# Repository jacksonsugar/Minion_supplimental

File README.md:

# Minion_supplimental
Additional docs for the Minion.

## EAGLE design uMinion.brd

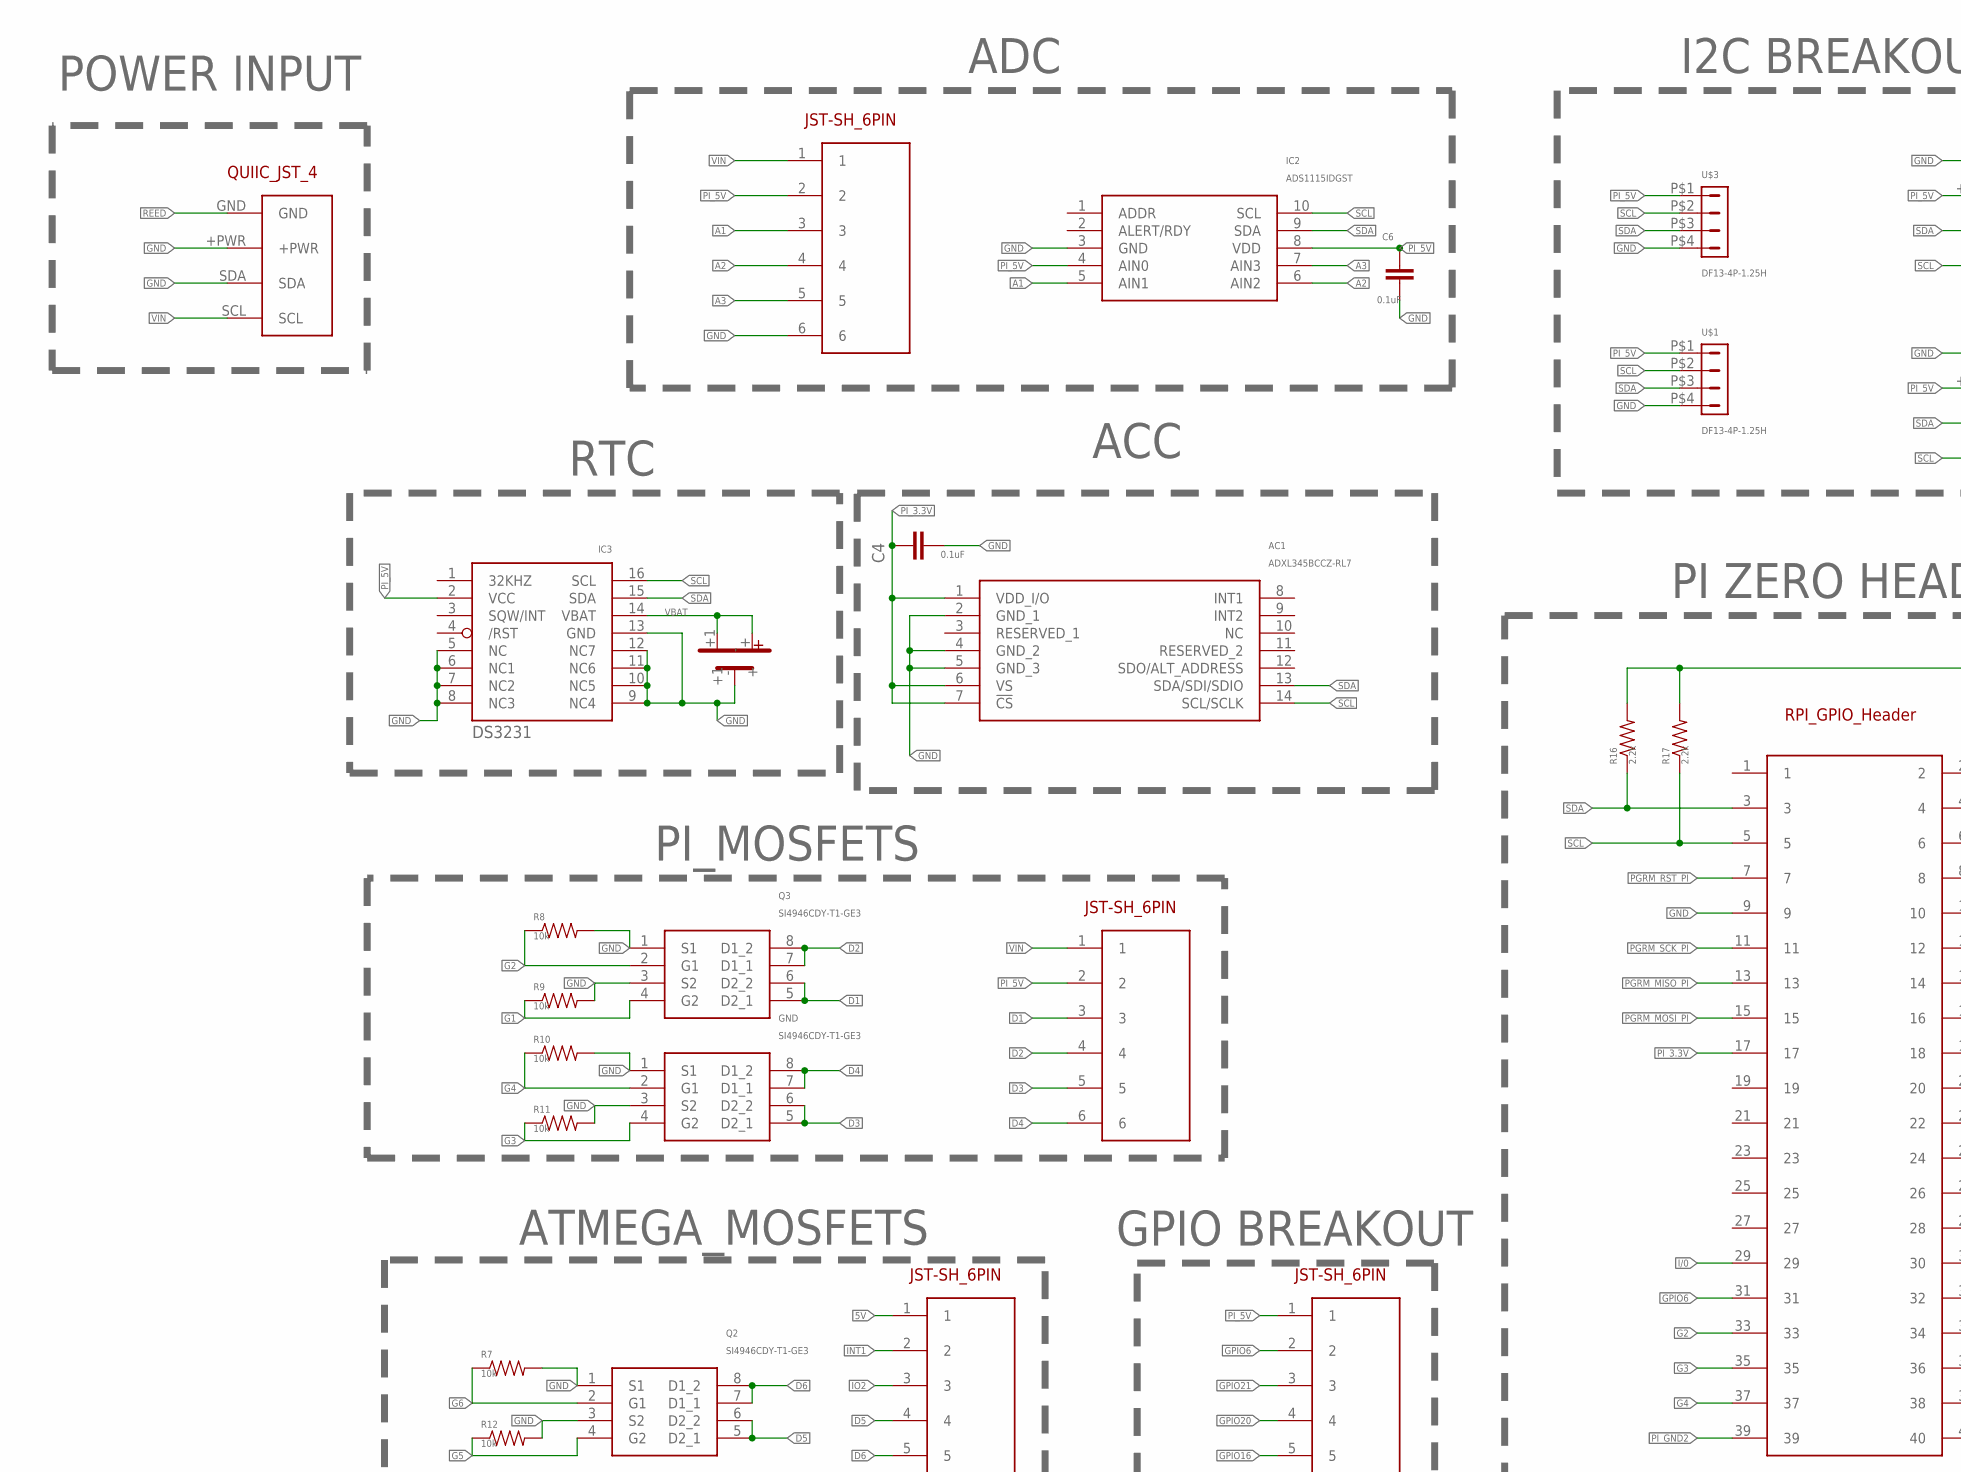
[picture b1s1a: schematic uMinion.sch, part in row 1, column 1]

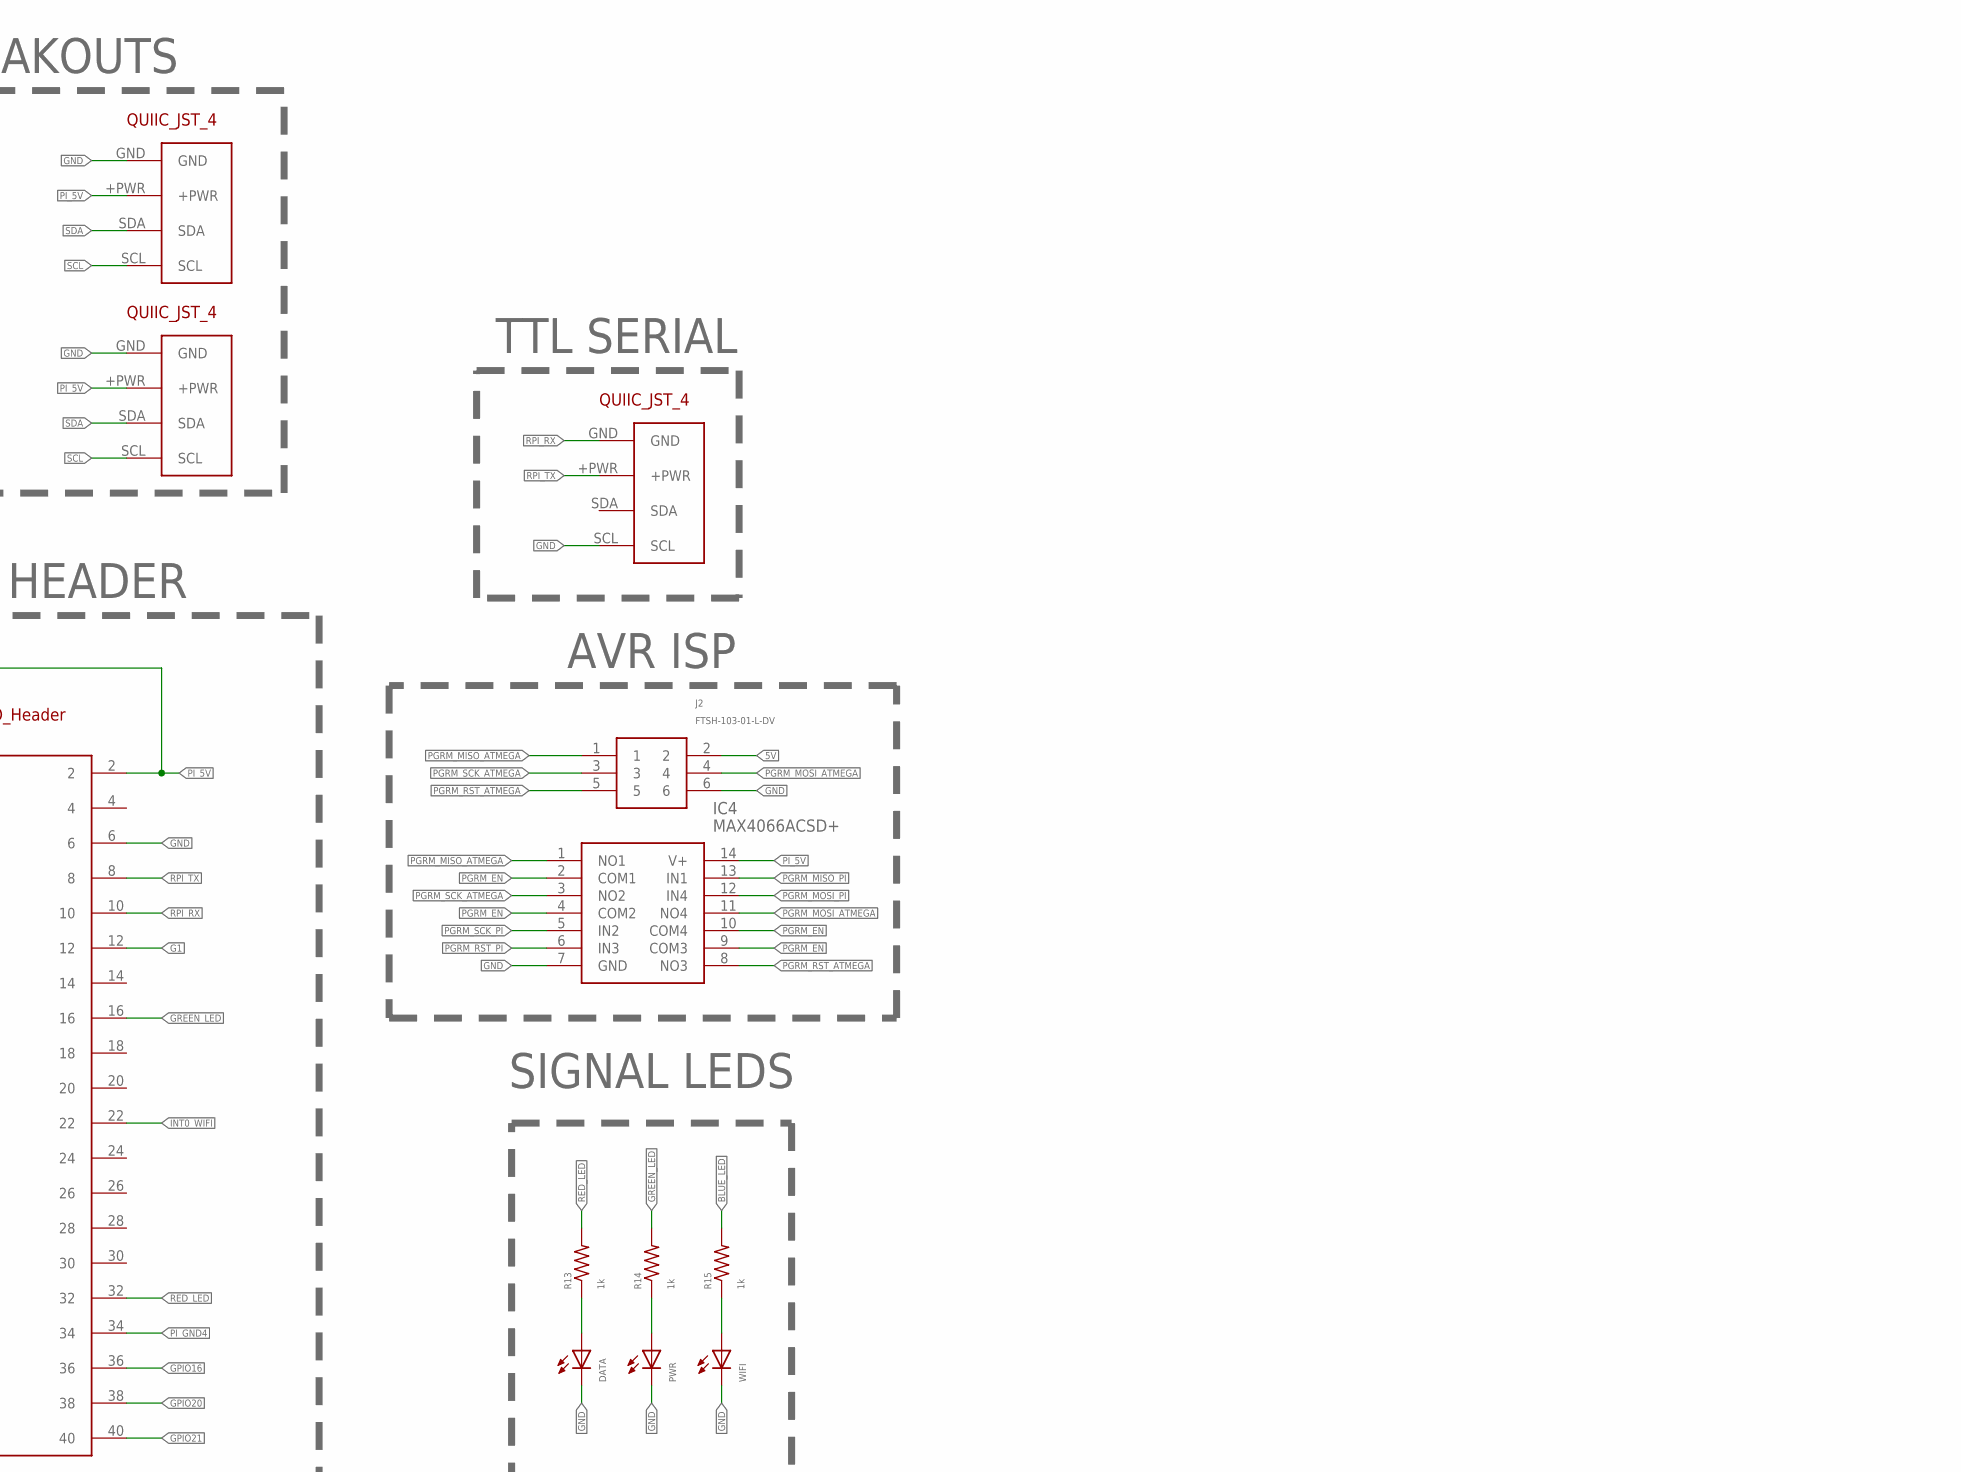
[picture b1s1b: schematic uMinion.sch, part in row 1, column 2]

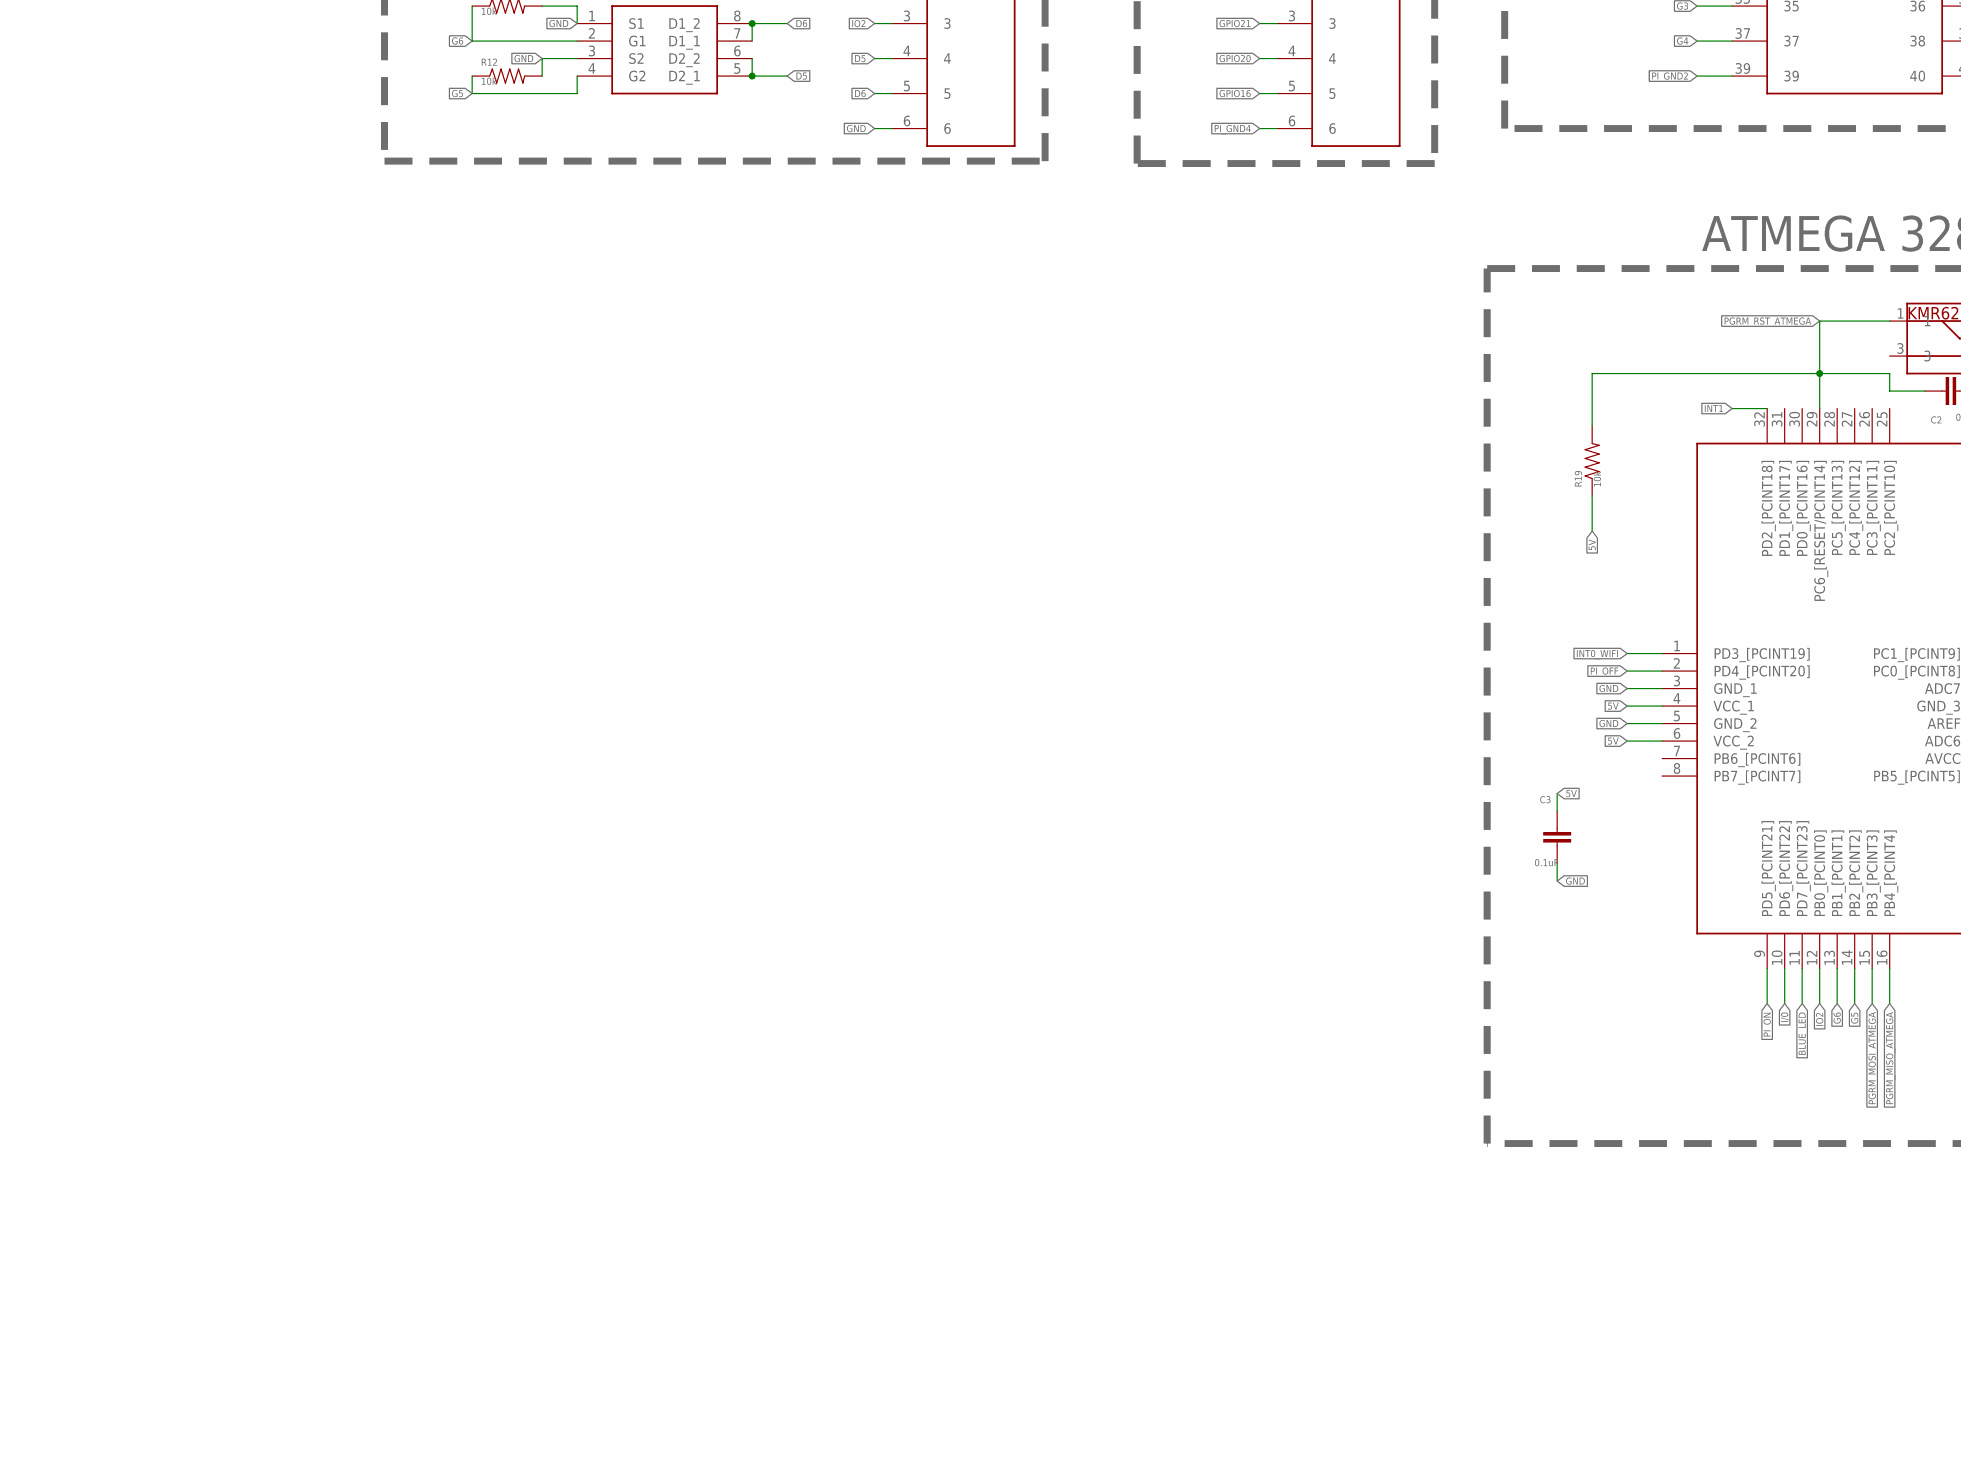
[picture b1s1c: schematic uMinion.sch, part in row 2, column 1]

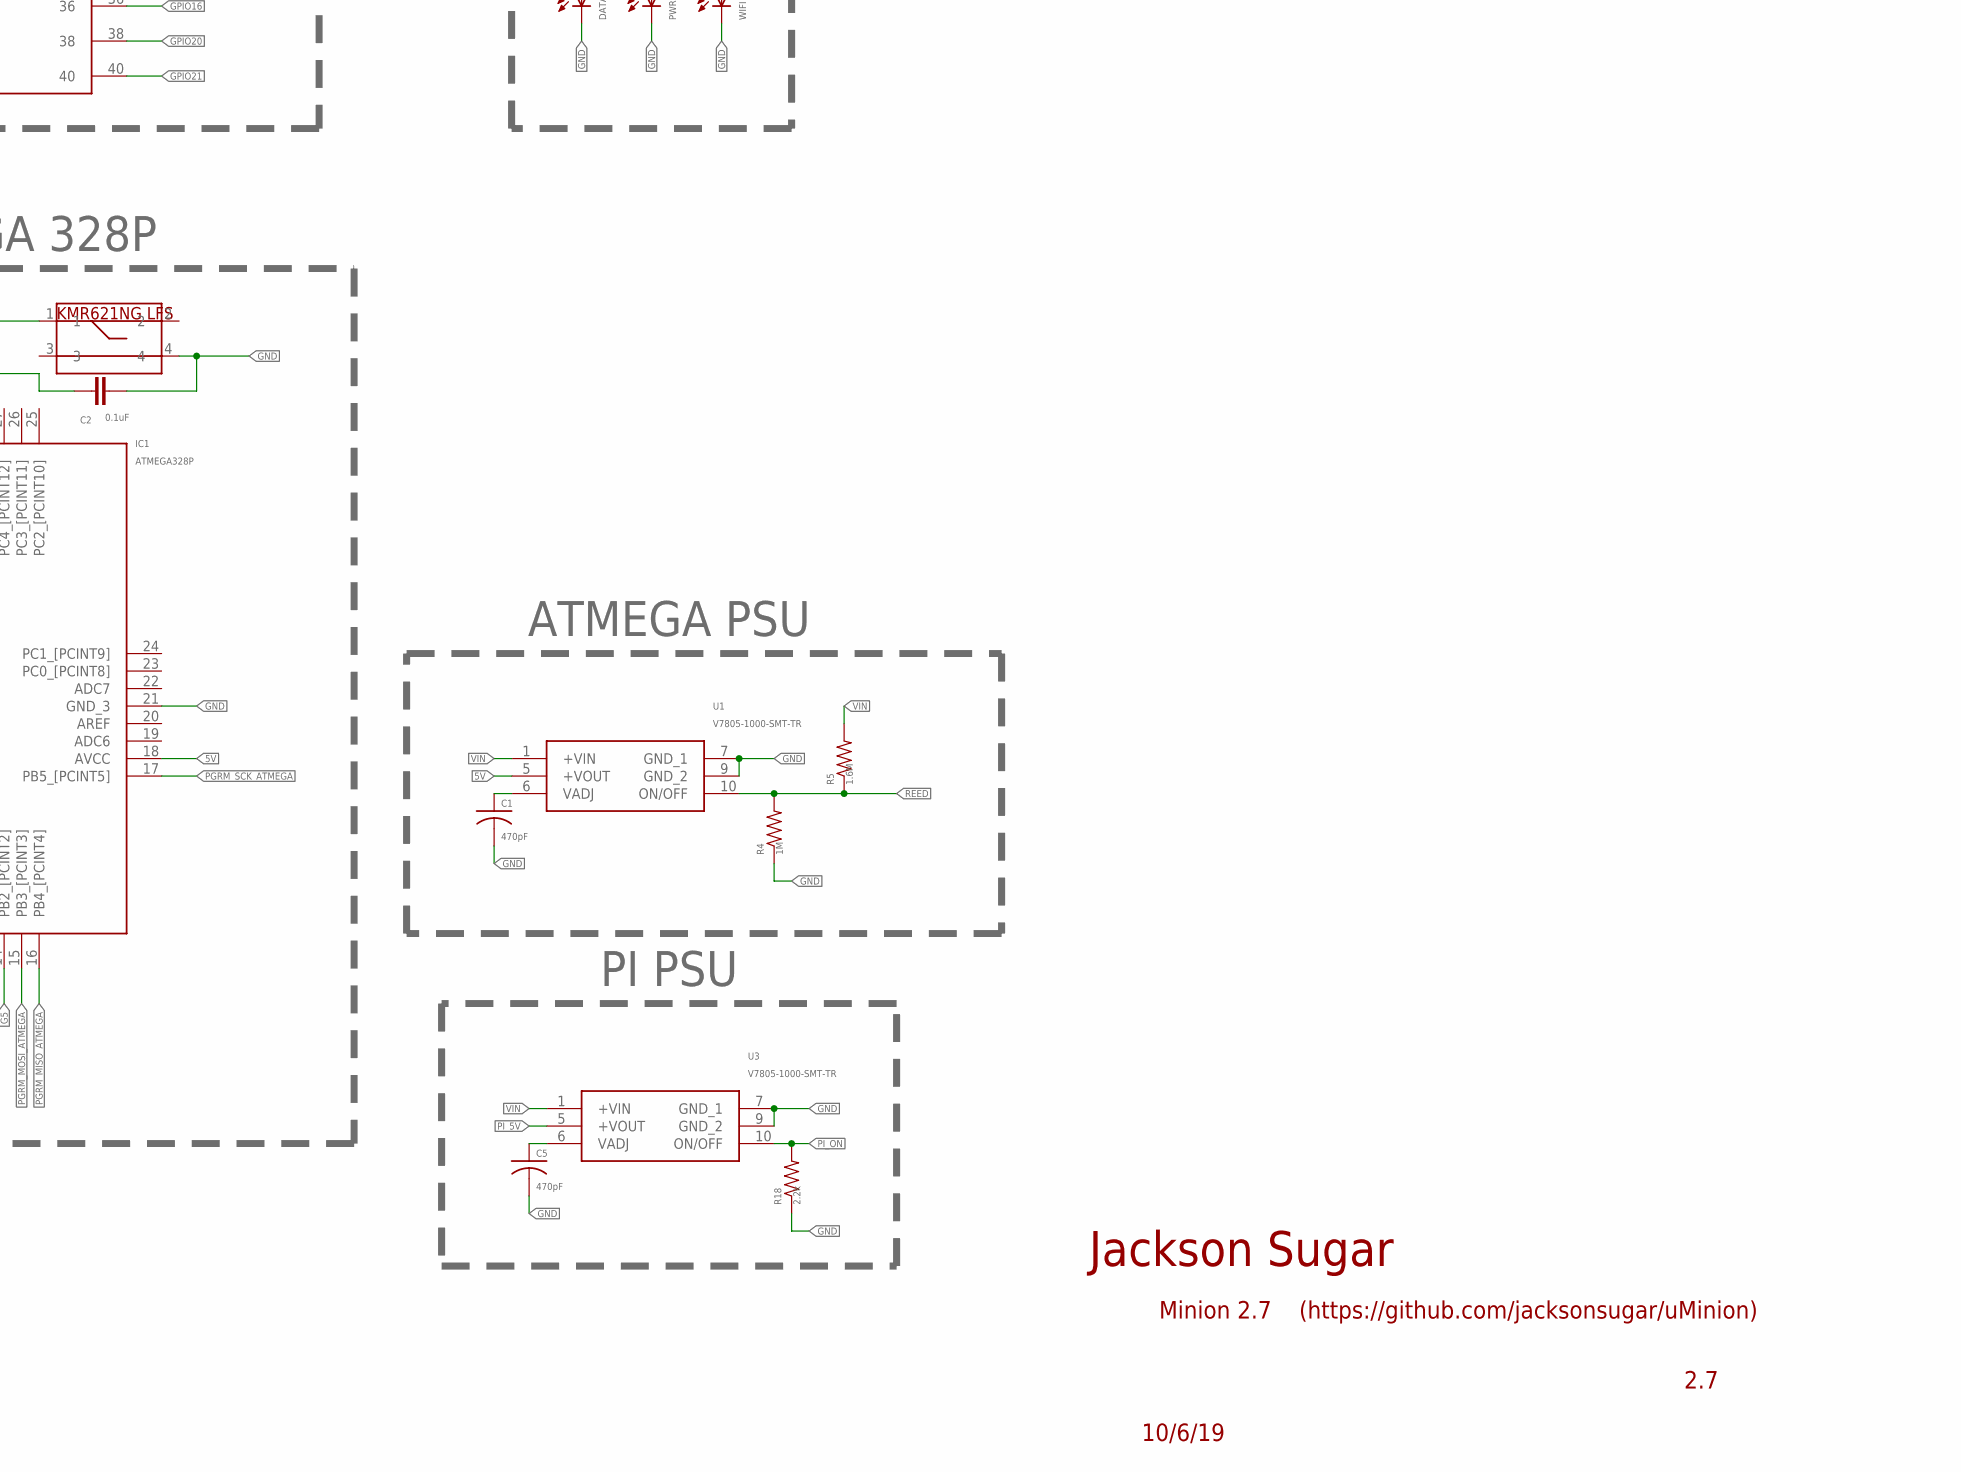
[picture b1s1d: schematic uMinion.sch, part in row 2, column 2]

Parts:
AC1: ADXL345BCCZ-RL7; CC-14-1
C1, C5: 470pF; C1206
C2, C3, C4, C6: 0.1uF; CAP_0805
DATA: LED_E; LED_1206
GND: SI4946CDY-T1-GE3; SOIC127P600X175-8N
IC1: ATMEGA328P; QFP80P900X900X120-32N
IC2: ADS1115IDGST; SOP50P490X110-10N
IC3: DS3231/SO; SO16W
IC4: MAX4066ACSD+; SOIC127P600X175-14N
J2: FTSH-103-01-L-DV; SAMTEC_FTSH-103-01-L-DV
PWR: LED_E; LED_1206
Q2, Q3: SI4946CDY-T1-GE3; SOIC127P600X175-8N
R4: 1M; 0603
R5: 1.6M; 0603
R7, R8, R9, R10, R11, R12, R19: 10k; 0603
R13, R14, R15: 1k; M1206
R16, R17, R18: 2.2k; 0603
U1, U3: V7805-1000-SMT-TR; V7805500SMTTR
U$1, U$3: DF13-4P-1.25H; DF13A-4P-1.25H
U$2, U$8, U$13, U$14: JST-SH_6PIN
U$5, U$6, U$7, U$10: QUIIC_JST_4
U$9: 40PIN_FEMALE_HEADER_SMD
U$11: CR1220_HOLDER
U$12: KMR621NGLFS
WIFI: LED_E; LED_1206

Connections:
5V: C3.1, IC1.4 (VCC_1), IC1.6 (VCC_2), IC1.18 (AVCC), J2.2, R19.1, U1.5 (+VOUT), U$14.1
A1: IC2.5 (AIN1), U$2.3
A2: IC2.6 (AIN2), U$2.4
A3: IC2.7 (AIN3), U$2.5
BLUE_LED: IC1.11 (PD7_[PCINT23]), R15.2
D1: Q3.5 (D2_1), Q3.6 (D2_2), U$8.3
D2: Q3.7 (D1_1), Q3.8 (D1_2), U$8.4
D3: GND.5 (D2_1), GND.6 (D2_2), U$8.5
D4: GND.7 (D1_1), GND.8 (D1_2), U$8.6
D5: Q2.5 (D2_1), Q2.6 (D2_2), U$14.4
D6: Q2.7 (D1_1), Q2.8 (D1_2), U$14.5
G1: Q3.4 (G2), R9.1, U$9.12
G2: Q3.2 (G1), R8.1, U$9.33
G3: GND.4 (G2), R11.1, U$9.35
G4: GND.2 (G1), R10.1, U$9.37
G5: IC1.14 (PB2_[PCINT2]), Q2.4 (G2), R12.1
G6: IC1.13 (PB1_[PCINT1]), Q2.2 (G1), R7.1
GND: AC1.2 (GND_1), AC1.4 (GND_2), AC1.5 (GND_3), C1.2, C2.2, C3.2, C4.2, C5.2, C6.2, DATA.C, GND.1 (S1), GND.3 (S2), IC1.3 (GND_1), IC1.5 (GND_2), IC1.21 (GND_3), IC2.3 (GND), IC3.5 (NC), IC3.6 (NC1), IC3.7 (NC2), IC3.8 (NC3), IC3.9 (NC4), IC3.10 (NC5), IC3.11 (NC6), IC3.12 (NC7), IC3.13 (GND), IC4.7 (GND), J2.6, PWR.C, Q2.1 (S1), Q2.3 (S2), Q3.1 (S1), Q3.3 (S2), R4.1, R7.2, R8.2, R9.2, R10.2, R11.2, R12.2, R18.1, U1.7 (GND_1), U1.9 (GND_2), U3.7 (GND_1), U3.9 (GND_2), U$1.P$4 (4), U$2.6, U$3.P$4 (4), U$5.SCL, U$6.GND, U$7.GND, U$9.6, U$9.9, U$10.+PWR, U$10.SDA, U$11.-, U$12.4, U$14.6, WIFI.C
GPIO6: U$9.31, U$13.2
GPIO16: U$9.36, U$13.5
GPIO20: U$9.38, U$13.4
GPIO21: U$9.40, U$13.3
GREEN_LED: R14.2, U$9.16
I/0: IC1.10 (PD6_[PCINT22]), U$9.29
INT0_WIFI: IC1.1 (PD3_[PCINT19]), U$9.22
INT1: IC1.32 (PD2_[PCINT18]), U$14.2
IO2: IC1.12 (PB0_[PCINT0]), U$14.3
unnamed: C1.1, U1.6 (VADJ)
unnamed: C5.1, U3.6 (VADJ)
unnamed: R15.1, WIFI.A
unnamed: DATA.A, R13.1
unnamed: PWR.A, R14.1
PGRM_EN: IC4.2 (COM1), IC4.4 (COM2), IC4.9 (COM3), IC4.10 (COM4)
PGRM_MISO_ATMEGA: IC1.16 (PB4_[PCINT4]), IC4.1 (NO1), J2.1
PGRM_MISO_PI: IC4.13 (IN1), U$9.13
PGRM_MOSI_ATMEGA: IC1.15 (PB3_[PCINT3]), IC4.11 (NO4), J2.4
PGRM_MOSI_PI: IC4.12 (IN4), U$9.15
PGRM_RST_ATMEGA: C2.1, IC1.29 (PC6_[RESET/PCINT14]), IC4.8 (NO3), J2.5, R19.2, U$12.1
PGRM_RST_PI: IC4.6 (IN3), U$9.7
PGRM_SCK_ATMEGA: IC1.17 (PB5_[PCINT5]), IC4.3 (NO2), J2.3
PGRM_SCK_PI: IC4.5 (IN2), U$9.11
PI_3.3V: AC1.1 (VDD_I/O), AC1.6 (VS), AC1.7 (!CS), C4.1, U$9.17
PI_5V: C6.1, IC2.4 (AIN0), IC2.8 (VDD), IC3.2 (VCC), IC4.14 (V+), R16.2, R17.2, U3.5 (+VOUT), U$1.P$1 (1), U$2.2, U$3.P$1 (1), U$6.+PWR, U$7.+PWR, U$8.2, U$9.2, U$13.1
PI_GND2: U$9.39
PI_GND4: U$9.34, U$13.6
PI_OFF: IC1.2 (PD4_[PCINT20])
PI_ON: IC1.9 (PD5_[PCINT21]), R18.2, U3.10 (ON/OFF)
RED_LED: R13.2, U$9.32
REED: R4.2, R5.1, U1.10 (ON/OFF), U$10.GND
RPI_RX: U$5.GND, U$9.10
RPI_TX: U$5.+PWR, U$9.8
SCL: AC1.14 (SCL/SCLK), IC2.10 (SCL), IC3.16 (SCL), R17.1, U$1.P$2 (2), U$3.P$2 (2), U$6.SCL, U$7.SCL, U$9.5
SDA: AC1.13 (SDA/SDI/SDIO), IC2.9 (SDA), IC3.15 (SDA), R16.1, U$1.P$3 (3), U$3.P$3 (3), U$6.SDA, U$7.SDA, U$9.3
VBAT: IC3.14 (VBAT), U$11.+, U$11.+1
VIN: R5.2, U1.1 (+VIN), U3.1 (+VIN), U$2.1, U$8.1, U$10.SCL

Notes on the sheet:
PI PSU
ADC
ACC
POWER INPUT
SIGNAL LEDS
PI ZERO HEADER
PI_MOSFETS
TTL SERIAL
I2C BREAKOUTS
ATMEGA 328P
RTC
ATMEGA PSU
AVR ISP
GPIO BREAKOUT
Minion 2.7
Jackson Sugar
10/6/19
(https://github.com/jacksonsugar/uMinion)
ATMEGA_MOSFETS
2.7

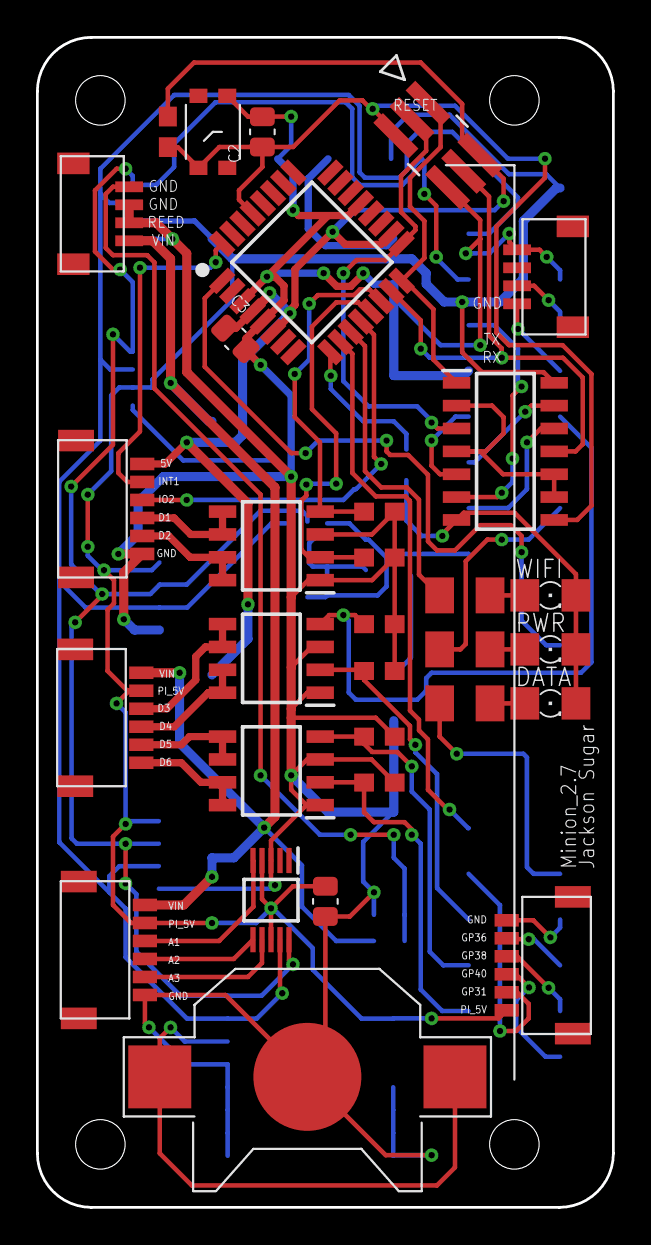
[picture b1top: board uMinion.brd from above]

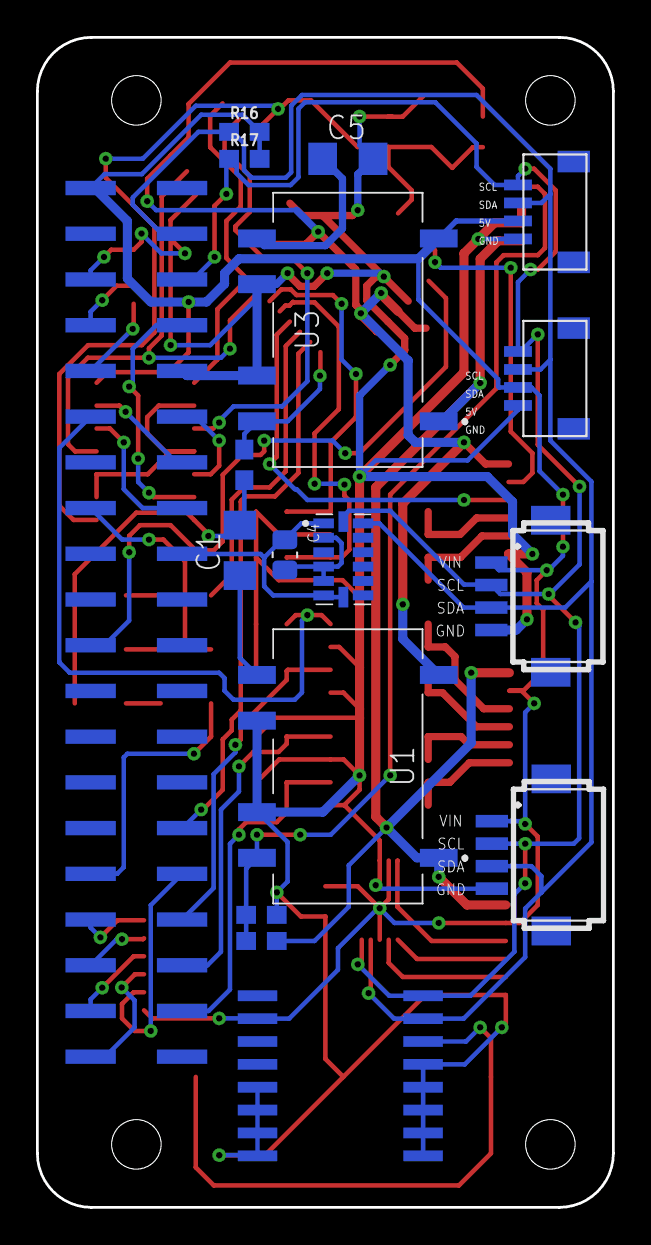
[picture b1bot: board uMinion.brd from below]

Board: 2 copper layers, 32.0 x 65.0 mm, 48 parts (16 on the bottom side), 53 nets.

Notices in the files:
parts and their libraries:
SparkFun-Resistors: Licensing: Creative Commons ShareAlike 4.0 International - https://creativecommons.org/licenses/by-sa/4.0
